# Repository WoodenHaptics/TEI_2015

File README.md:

# TEI_2015

Welcome! On this repository you will find the information you need to start fabricating your own grounded spatial haptic device based on our default open source design. This site is essentially the companion to our TEI2015 conference paper WoodenHaptics: A Starting Kit for Crafting Force-Reflecting Spatial Haptic Devices. We hope you want to share our joy of crafting haptic devices!

more information on this device and its construction in our website:
www.woodenhaptics.org

Please start with reading the website and the research paper found on the website.

The license for this whole project is CC-BY-SA 4.0 if nothing else mentioned. 
The CHAI3D extension software is BSD-licensed like its parent project. 
Are you interesed in other licensing agreements or like to distribute the kit, email jofo02 at kth.se

/ Jonas, Mike and Jordi - January 17th 2015

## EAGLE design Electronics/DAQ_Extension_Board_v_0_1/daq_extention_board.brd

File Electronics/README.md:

# Main_board_EAGLE_v_0_1

Eagle files for the main board version 0.1

This is the first version of the wooden haptics driver. This bord will accept 3 motors up to 3Amps each and 3 decoders. It has been designed to host ESCON motor drivers:

http://www.maxonmotor.com/maxon/view/product/control/4-Q-Servokontroller/438725

The same ESCON sockets can be used to connect any other DC motor driver if conencting to the propper pin connectors (PWR, motor out and PWM)

THis board can be used with and external DAQ (using the extension board) board or a mBed M3 Cortex:

https://www.sparkfun.com/products/9564

The elctronics are powerd up over USB but in order to power the motors it requires an external power supply 12v-48v, depending on the motors used.

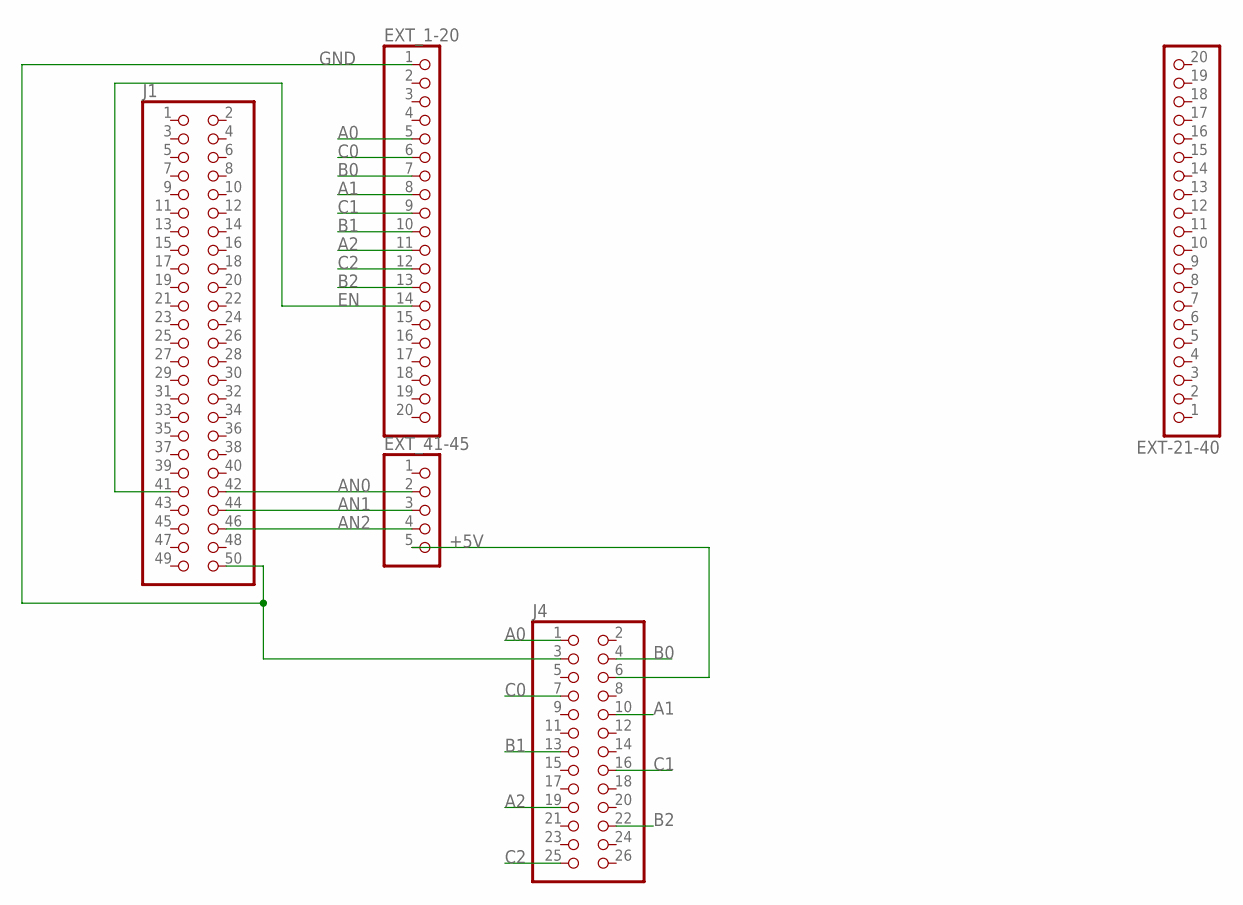
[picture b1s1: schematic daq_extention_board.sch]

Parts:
EXT-21-40: PINHD-1X20; 1X20
EXT_1-20: PINHD-1X20; 1X20
EXT_41-45: PINHD-1X5; 1X05
J1: PINHD-2X25; 2X25
J4: PINHD-2X13; 2X13

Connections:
+5V: EXT_41-45.5, J4.6
A0: EXT_1-20.5, J4.1
A1: EXT_1-20.8, J4.10
A2: EXT_1-20.11, J4.19
AN0: EXT_41-45.2, J1.42
AN1: EXT_41-45.3, J1.44
AN2: EXT_41-45.4, J1.46
B0: EXT_1-20.7, J4.4
B1: EXT_1-20.10, J4.13
B2: EXT_1-20.13, J4.22
C0: EXT_1-20.6, J4.7
C1: EXT_1-20.9, J4.16
C2: EXT_1-20.12, J4.25
EN: EXT_1-20.14, J1.41
GND: EXT_1-20.1, J1.50, J4.3

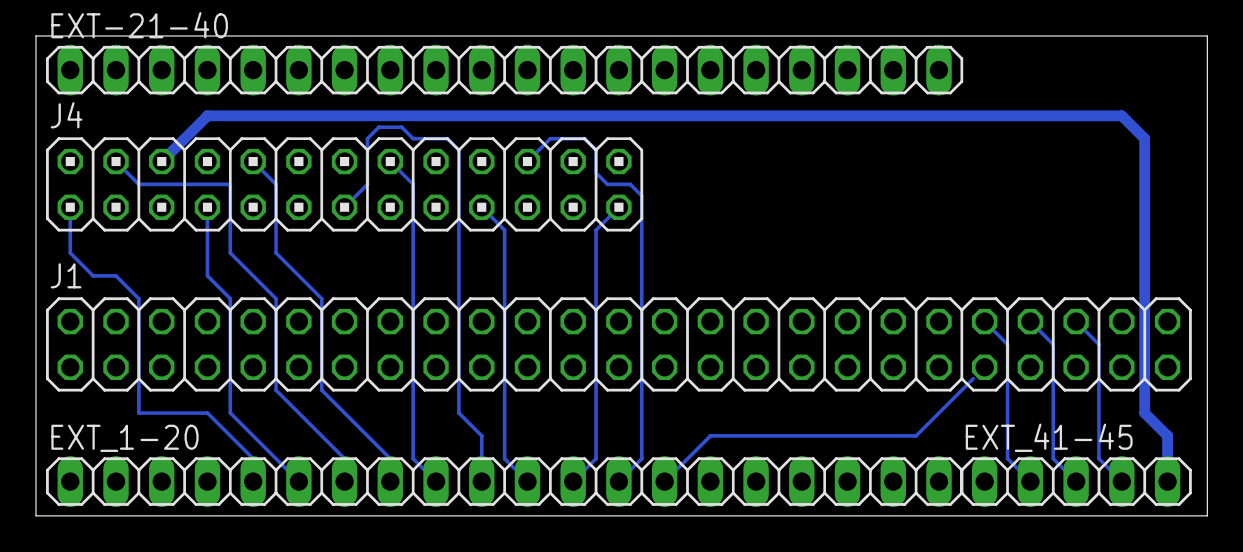
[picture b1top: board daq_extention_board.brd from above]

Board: 2 copper layers, 65.1 x 26.7 mm, 5 parts (0 on the bottom side), 15 nets.

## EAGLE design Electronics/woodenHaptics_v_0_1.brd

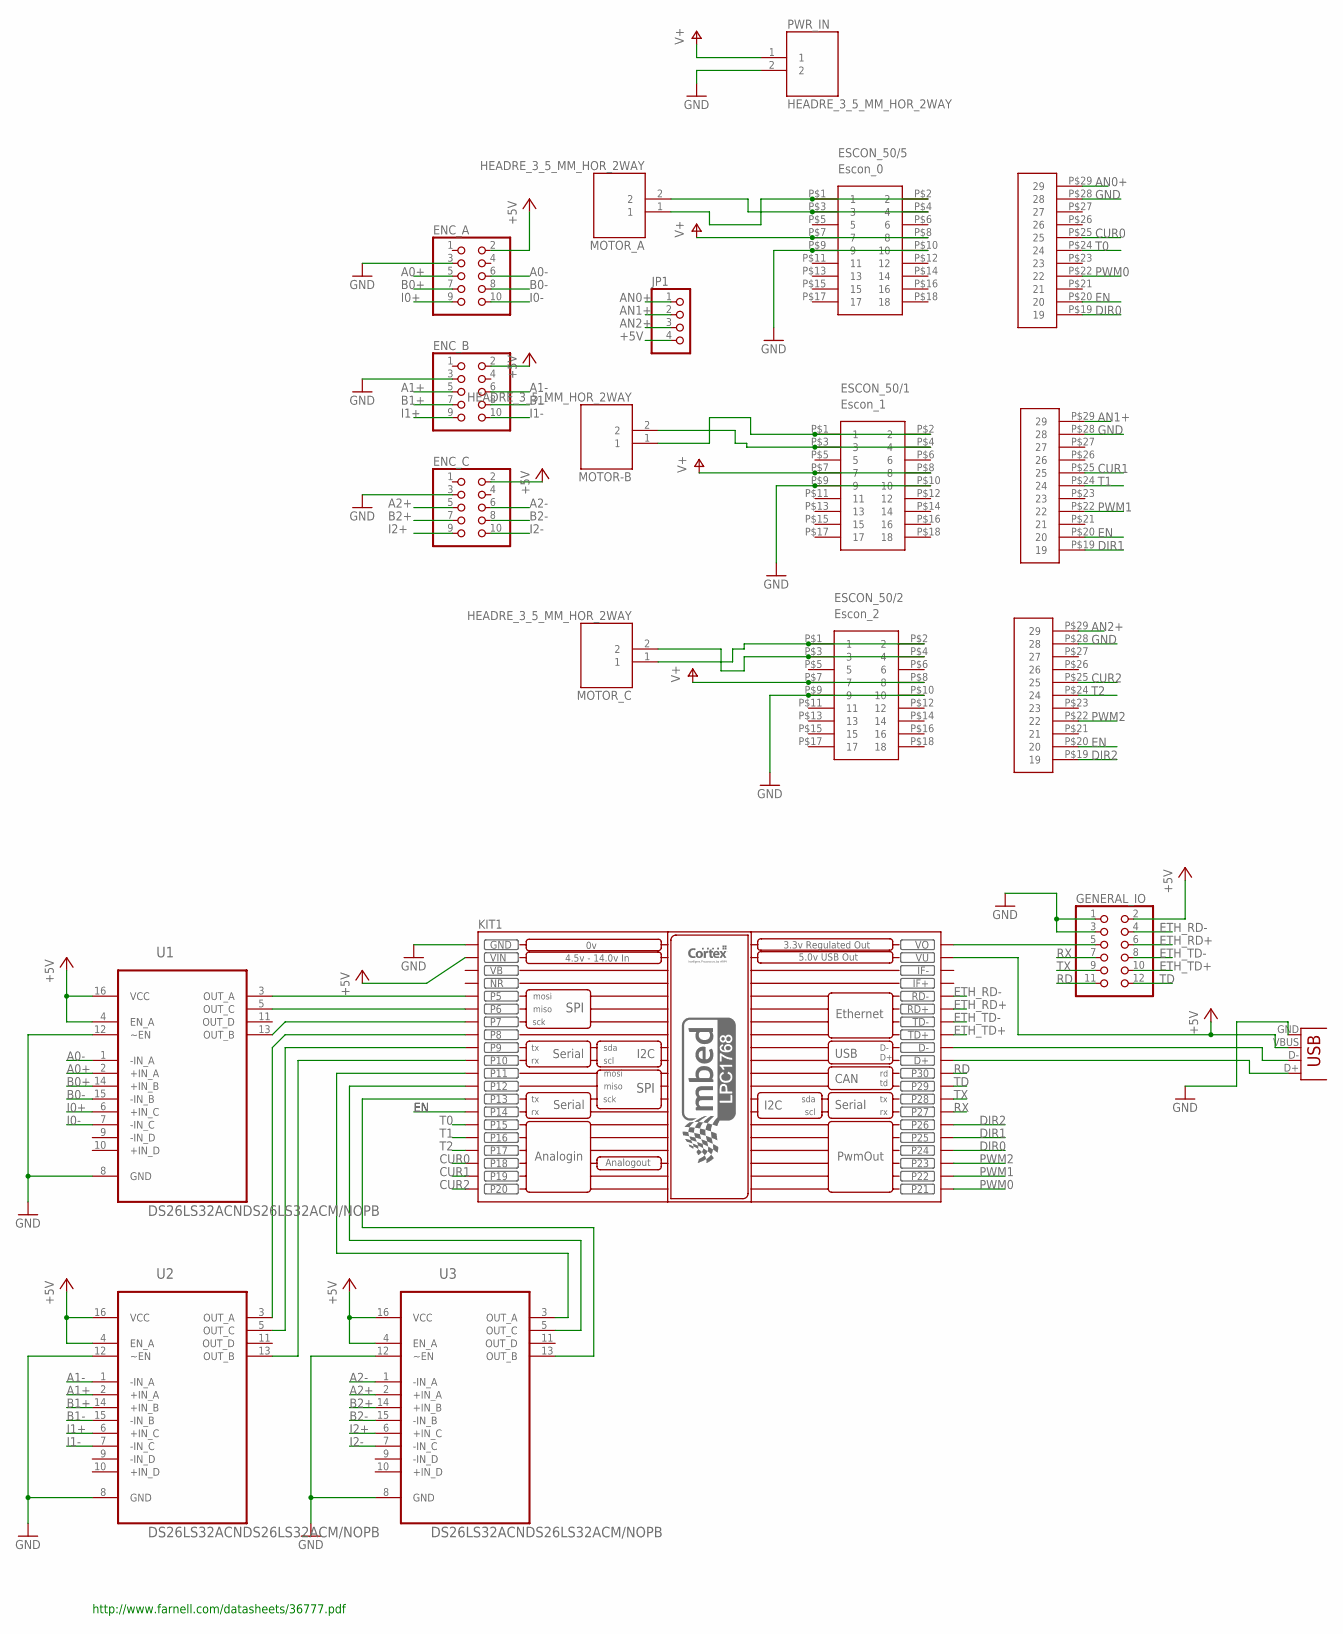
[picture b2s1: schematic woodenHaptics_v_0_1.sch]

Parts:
ENC_A: PINHD-2X5; 2X05
ENC_B: PINHD-2X5; 2X05
ENC_C: PINHD-2X5; 2X05
ESCON_50/1: Escon_1; MODULE
ESCON_50/2: Escon_2; MODULE
ESCON_50/5: Escon_0; MODULE
GENERAL_IO: PINHD-2X6; 2X06
JP1: PINHD-1X4; 1X04
KIT1: MBED_NXP_LPC1768; MBED-KIT
MOTOR-B: HEADRE_3_5_MM_HOR_2WAY; HEADER_3_5MM_HOR_2WAY
MOTOR_A: HEADRE_3_5_MM_HOR_2WAY; HEADER_3_5MM_HOR_2WAY
MOTOR_C: HEADRE_3_5_MM_HOR_2WAY; HEADER_3_5MM_HOR_2WAY
PWR_IN: HEADRE_3_5_MM_HOR_2WAY; HEADER_3_5MM_HOR_2WAY
U1, U2, U3: DS26LS32ACNDS26LS32ACM/NOPB; M16
X2: Micro USB; USB-MICROB

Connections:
+5V: ENC_A.2, ENC_B.2, ENC_C.2, GENERAL_IO.2, JP1.4, KIT1.VIN, KIT1.VU, U1.4 (EN_A), U1.16 (VCC), U2.4 (EN_A), U2.16 (VCC), U3.4 (EN_A), U3.16 (VCC), X2.VBUS
A0+: ENC_A.5, U1.2 (+IN_A)
A0-: ENC_A.6, U1.1 (-IN_A)
A1+: ENC_B.5, U2.2 (+IN_A)
A1-: ENC_B.6, U2.1 (-IN_A)
A2+: ENC_C.5, U3.2 (+IN_A)
A2-: ENC_C.6, U3.1 (-IN_A)
AN0+: ESCON_50/5.P$29 (29), JP1.1
AN1+: ESCON_50/1.P$29 (29), JP1.2
AN2+: ESCON_50/2.P$29 (29), JP1.3
B0+: ENC_A.7, U1.14 (+IN_B)
B0-: ENC_A.8, U1.15 (-IN_B)
B1+: ENC_B.7, U2.14 (+IN_B)
B1-: ENC_B.8, U2.15 (-IN_B)
B2+: ENC_C.7, U3.14 (+IN_B)
B2-: ENC_C.8, U3.15 (-IN_B)
CUR0: ESCON_50/5.P$25 (25), KIT1.P$18 (P18)
CUR1: ESCON_50/1.P$25 (25), KIT1.P$19 (P19)
CUR2: ESCON_50/2.P$25 (25), KIT1.P$20 (P20)
DIR0: ESCON_50/5.P$19 (19), KIT1.P$24 (P24)
DIR1: ESCON_50/1.P$19 (19), KIT1.P$25 (P25)
DIR2: ESCON_50/2.P$19 (19), KIT1.P$26 (P26)
EN: ESCON_50/1.P$20 (20), ESCON_50/2.P$20 (20), ESCON_50/5.P$20 (20), KIT1.P$14 (P14)
ETH_RD+: GENERAL_IO.6, KIT1.RD+
ETH_RD-: GENERAL_IO.4, KIT1.RD-
ETH_TD+: GENERAL_IO.10, KIT1.TD+
ETH_TD-: GENERAL_IO.8, KIT1.TD-
GND: ENC_A.3, ENC_B.3, ENC_C.3, ESCON_50/1.P$9 (9), ESCON_50/1.P$10 (10), ESCON_50/1.P$28 (28), ESCON_50/2.P$9 (9), ESCON_50/2.P$10 (10), ESCON_50/2.P$28 (28), ESCON_50/5.P$9 (9), ESCON_50/5.P$10 (10), ESCON_50/5.P$28 (28), GENERAL_IO.1, GENERAL_IO.3, KIT1.GND, PWR_IN.2, U1.8 (GND), U1.12 (~EN), U2.8 (GND), U2.12 (~EN), U3.8 (GND), U3.12 (~EN), X2.GND
I0+: ENC_A.9, U1.6 (+IN_C)
I0-: ENC_A.10, U1.7 (-IN_C)
I1+: ENC_B.9, U2.6 (+IN_C)
I1-: ENC_B.10, U2.7 (-IN_C)
I2+: ENC_C.9, U3.6 (+IN_C)
I2-: ENC_C.10, U3.7 (-IN_C)
unnamed: ESCON_50/5.P$3 (3), ESCON_50/5.P$4 (4), MOTOR_A.2
unnamed: ESCON_50/1.P$1 (1), ESCON_50/1.P$2 (2), MOTOR-B.1
unnamed: KIT1.D-, X2.D-
unnamed: ESCON_50/1.P$3 (3), ESCON_50/1.P$4 (4), MOTOR-B.2
unnamed: ESCON_50/2.P$1 (1), ESCON_50/2.P$2 (2), MOTOR_C.1
unnamed: ESCON_50/2.P$3 (3), ESCON_50/2.P$4 (4), MOTOR_C.2
unnamed: KIT1.D+, X2.D+
unnamed: KIT1.P$8 (P8), U2.3 (OUT_A)
unnamed: GENERAL_IO.5, KIT1.VOUT (VO)
unnamed: KIT1.P$5 (P5), U1.3 (OUT_A)
unnamed: KIT1.P$6 (P6), U1.5 (OUT_C)
unnamed: KIT1.P$7 (P7), U1.13 (OUT_B)
unnamed: KIT1.P$9 (P9), U2.5 (OUT_C)
unnamed: KIT1.P$10 (P10), U2.13 (OUT_B)
unnamed: KIT1.P$11 (P11), U3.3 (OUT_A)
unnamed: KIT1.P$12 (P12), U3.5 (OUT_C)
unnamed: KIT1.P$13 (P13), U3.13 (OUT_B)
unnamed: ESCON_50/5.P$1 (1), ESCON_50/5.P$2 (2), MOTOR_A.1
NR: KIT1.NR
PWM0: ESCON_50/5.P$22 (22), KIT1.P$21 (P21)
PWM1: ESCON_50/1.P$22 (22), KIT1.P$22 (P22)
PWM2: ESCON_50/2.P$22 (22), KIT1.P$23 (P23)
RD: GENERAL_IO.11, KIT1.P$30 (P30)
RX: GENERAL_IO.7, KIT1.P$27 (P27)
T0: ESCON_50/5.P$24 (24), KIT1.P$15 (P15)
T1: ESCON_50/1.P$24 (24), KIT1.P$16 (P16)
T2: ESCON_50/2.P$24 (24), KIT1.P$17 (P17)
TD: GENERAL_IO.12, KIT1.P$29 (P29)
TX: GENERAL_IO.9, KIT1.P$28 (P28)
V+: ESCON_50/1.P$7 (7), ESCON_50/1.P$8 (8), ESCON_50/2.P$7 (7), ESCON_50/2.P$8 (8), ESCON_50/5.P$7 (7), ESCON_50/5.P$8 (8), PWR_IN.1
VB: KIT1.VB

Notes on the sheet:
http://www.farnell.com/datasheets/36777.pdf

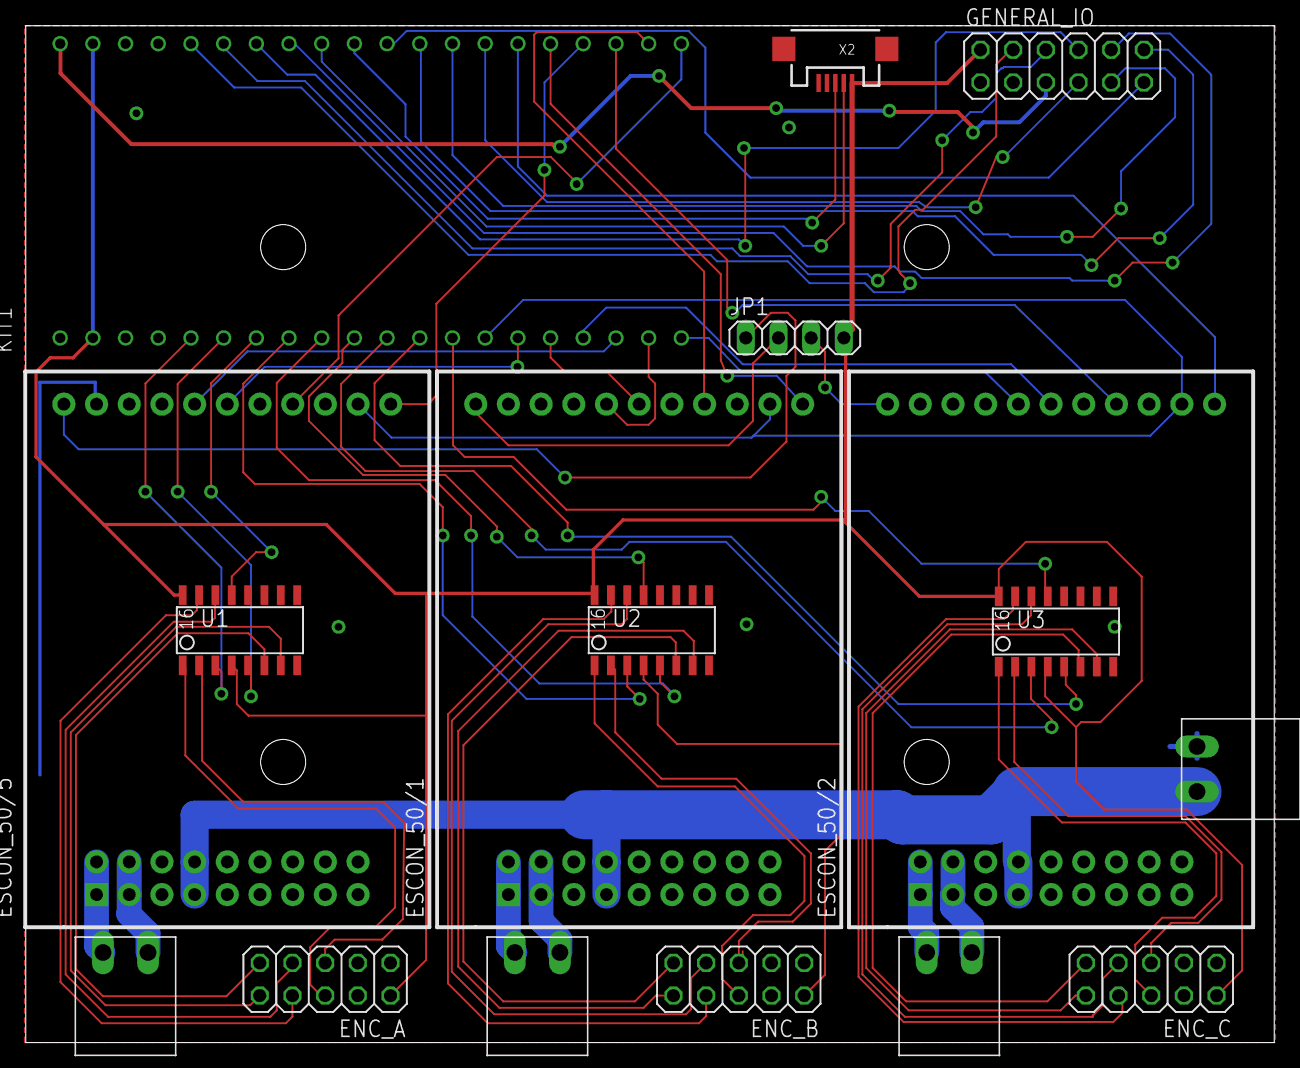
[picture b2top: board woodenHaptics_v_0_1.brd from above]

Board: 2 copper layers, 97.0 x 79.0 mm, 17 parts (0 on the bottom side), 63 nets.

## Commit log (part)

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2015-01-17 first commit
    first commit
2015-01-17 Software, electronics case etc
2015-01-22 clarified licence
2015-01-23 vent holes (and text) added to electronics case
2015-01-24 escon configuation screenshots
2015-02-05 config file
2015-02-05 pdf update
    pdf update
2015-05-26 reference order pcb
2015-06-02 Added illustrator lasercut files
2016-06-04 updated with cutlasercut-verified .ai files
2017-03-08 added encoder doc
2017-04-26 lasercut box 2017 (version 0.4)
2019-05-18 bom archived
